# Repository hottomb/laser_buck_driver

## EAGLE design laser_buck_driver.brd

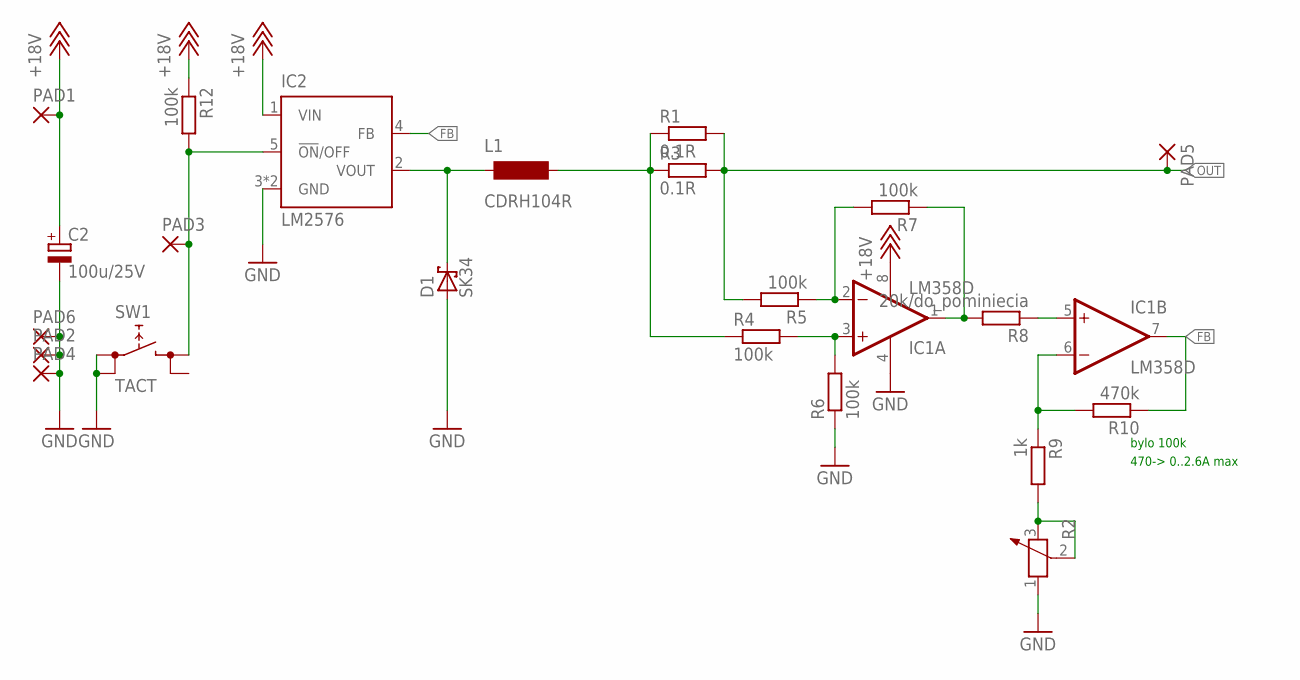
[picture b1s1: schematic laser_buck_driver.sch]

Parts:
C2: 100u/25V; 153CLV-0810
D1: SK34; SMA(DO214-AC)
IC1: LM358D; SO08
IC2: LM2576; TO263-5
L1: CDRH104R; CDRH104-R
PAD1, PAD2, PAD3, PAD4, PAD5, PAD6: SMD2; SMD1,27-2,54
R1, R3: 0.1R; R1206
R2: POTENTIOMETER_; RTRIM_SMD_CUSTOM
R4, R5, R6, R7: 100k; R0805
R8: 20k/do_pominiecia; R0805
R9: 1k; R0805
R10: 470k; R0805
R12: 100k; R1206
SW1: TACT

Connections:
22K: IC1.5 (+IN), R8.1
+18V: C2.+, IC1.8 (V+), IC2.1 (VIN), PAD1.1, R12.1
FB: IC1.7 (OUT), IC2.4 (FB), R10.1
GND: C2.-, D1.A, IC1.4 (V-), IC2.3 (GND), IC2.6 (GND), PAD2.1, PAD4.1, PAD6.1, R2.1, R6.1, SW1.1, SW1.4
unnamed: D1.C, IC2.2 (VOUT), L1.1
unnamed: IC2.5 (!ON!/OFF), PAD3.1, R12.2, SW1.2
unnamed: IC1.1 (OUT), R7.1, R8.2
unnamed: L1.2, R1.1, R3.1, R4.1
unnamed: IC1.6 (-IN), R9.1, R10.2
unnamed: IC1.2 (-IN), R5.1, R7.2
unnamed: IC1.3 (+IN), R4.2, R6.2
unnamed: R2.2 (3), R2.3 (2), R9.2
OUT: PAD5.1, R1.2, R3.2, R5.2

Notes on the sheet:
bylo 100k
470-> 0..2.6A max

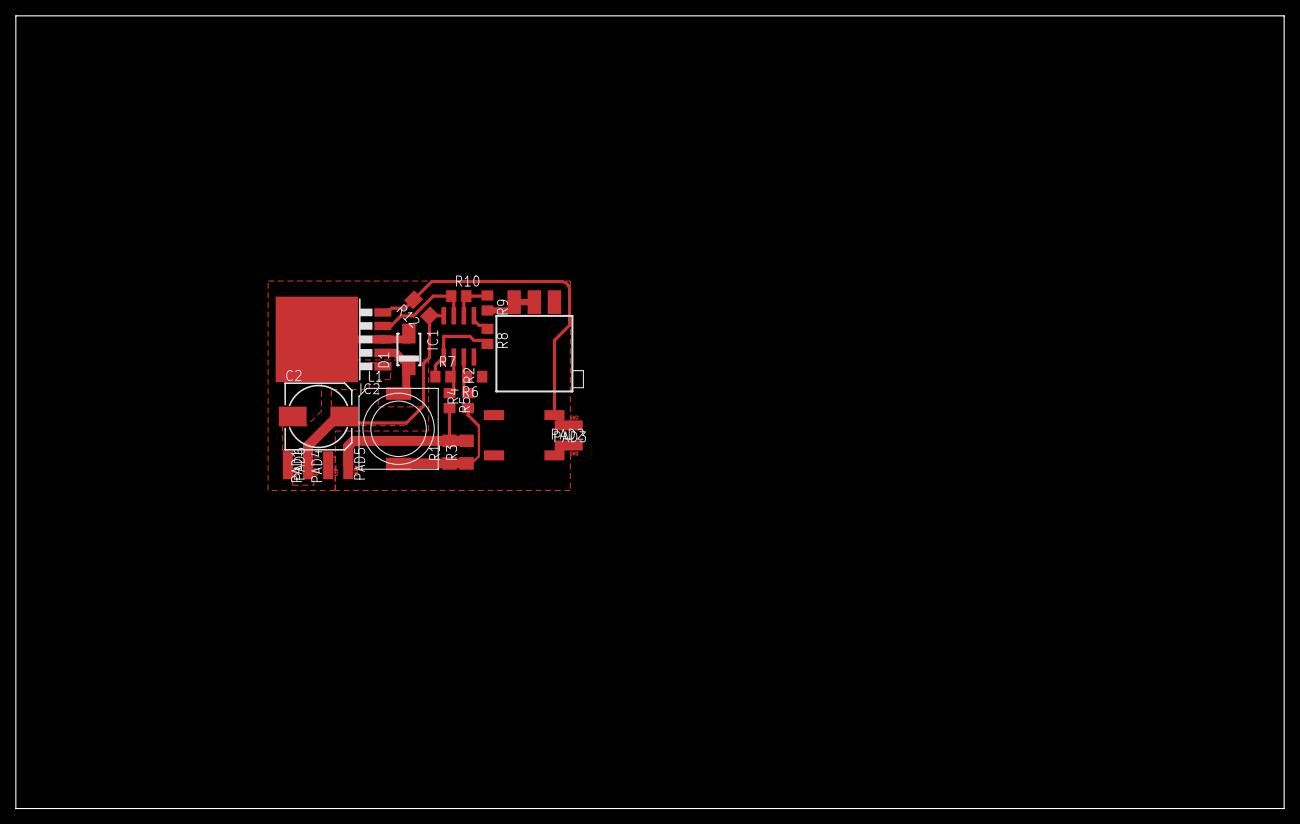
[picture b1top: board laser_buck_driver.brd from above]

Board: 2 copper layers, 160.0 x 100.0 mm, 23 parts (0 on the bottom side), 13 nets.

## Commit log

2017-12-21 PCB layout complete
2018-01-06 test_release
2018-08-27 comments
    screenshot and minor updates
